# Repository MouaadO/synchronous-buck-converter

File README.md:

# 58 W Synchronous Buck Converter

**37.8–58.8 V input · 14.5 V / 4 A output target · 100 kHz · Discrete gate drivers**

This project develops a DC–DC buck converter for the auxiliary electrical network of an electric scooter. It steps the traction-battery voltage down to a 14.5 V service supply, with a design power of **58 W**. The work covers the switching stage, discrete transistor gate drivers, current and voltage sensing, LTspice simulation, and a complete two-layer KiCad PCB.

**Project team:** Amani Mouaad and Cheiffou Melissa  
**IFP SCHOOL · Powertrain · 2026/2027**

## Two projects, one conversion system

This power board is the second part of the [analog PWM generator project](https://github.com/MouaadO/analog-pwm-generator). The first board generates two complementary 5 V PWM commands with adjustable dead time. The buck board receives those signals through Arduino Uno Rev3-compatible headers, amplifies them with discrete drivers, and switches the power MOSFETs.

```mermaid
flowchart LR
    B["Scooter traction battery\n37.8–58.8 V"] --> F["Input filter"]
    F --> H["MOSFET half bridge"]
    H --> LC["Inductor + output capacitor"]
    LC --> O["Service network\n14.5 V · up to 4 A target"]
    P["Project 1\nAnalog PWM generator"] -->|"PWM1 / PWM2 + GND"| D["Discrete gate drivers\n12 V supply"]
    D --> H
    H --> M["Voltage and current sensing"]
    LC --> M
    M --> A["Analog measurement outputs\nArduino A0–A4"]
```

The intended scooter application is the **auxiliary/service electrical network**. The power path and PWM command board form an open-loop demonstrator; the measurement outputs provide an interface for later control development.

## Design targets from the project brief

| Parameter | Target |
|---|---:|
| Converter topology | Non-isolated synchronous buck |
| Battery input range | 37.8–58.8 V DC |
| Output voltage | 14.5 V |
| Maximum output current | 4 A |
| Maximum output power | 58 W |
| Switching frequency | 100 kHz |
| Inductor current ripple | 0.8 A peak to peak |
| Minimum inductance specified in the brief | 137 µH |
| Output voltage ripple target | Below 0.1% of output voltage |
| Measurement interface | 0–5 V analog signals |
| PCB outline | 166 × 53 mm |

These values are the **design specifications**, separate from the LTspice results below. The requirements come from the course mini-project brief, *Conception d’un convertisseur abaisseur de tension à redressement synchrone et de son étage de commande bas niveau*, especially pages 4–5 and 9–12.

At the rated operating point:

$$P_{out}=V_{out}I_{out}=14.5\times4=58\ \mathrm{W}$$

For an ideal buck converter, $D\approx V_{out}/V_{in}$, giving an approximate duty range of **24.7–38.4%** across the specified input range. At 100 kHz, one switching period is **10 µs**. [Design notes](docs/design.md) explain the operating sequence, component roles and sizing equations.

## How the circuit works

1. **Input filtering:** L1 filters the battery input. The 100 µF input capacitor C15 and R10 form the series damping branch used in `Newinputfilter.asc`.
2. **Discrete drivers:** NPN/PNP transistor stages translate the incoming PWM signals into MOSFET gate-drive signals. The high-side stage uses a bootstrap diode and capacitor to create a floating supply referenced to the switching node.
3. **Power conversion:** The high-side MOSFET applies the filtered input to the inductor. The low-side MOSFET provides the synchronous current path during the other part of the cycle. Complementary PWM and dead time come from the first project.
4. **Output smoothing:** The wound E25/13/7 N87 inductor and the output capacitor smooth the switched waveform into a DC output.
5. **Measurements:** Shunts, differential amplifiers, dividers and filters expose input voltage, output voltage, inductor current, filtered current and low-side current signals.

## PCB and mechanical design

The board uses **two copper layers**, predominantly through-hole components, project-local footprints and bundled 3D models. The power section groups the MOSFETs, input capacitor, shunt and output inductor. The driver components sit close to the switching stage, while measurement circuitry occupies the lower-power region.

Main load-current tracks are 2.5 mm wide, with shorter 1.2 mm connections at selected pads. Measurement tracks are 0.3 mm; gate-resistor breakouts use 0.5 mm tracks. Ground fills connect the common return network on both copper layers. A bottom-layer keepout under the switching-node area controls nearby copper placement.

### Top view

### Connection to the PWM board

The underside headers J4–J7 mate with the PWM board. The render illustrates the two-board arrangement; spacer height is an assembly choice.

| Signal | Buck connection | Uno contact |
|---|---|---|
| High-side PWM command | J4 pin 9 | D9 |
| Low-side PWM command | J4 pin 8 | D10 |
| Common ground | J4 pin 4; J6 pins 6–7 | GND |
| Input voltage measurement | J7 pin 1 | A0 |
| Output voltage measurement | J7 pin 2 | A1 |
| Inductor current measurement | J7 pin 3 | A2 |
| Filtered current measurement | J7 pin 4 | A3 |
| Low-side current measurement | J7 pin 5 | A4 |

The power input, 12 V driver supply and output load connect through separate screw terminals. [Connections and assembly](docs/connections.md) provides the complete connector map.

### Underside and stacking contacts

The downward-facing header pins connect the power board to the PWM generator. Project identification is printed on the back silkscreen.

### Front and back routing

| Front copper | Back copper |
|---|---|
|  |  |

### Heatsink and inductor mounting

The high-side MOSFET uses a TO-220 heatsink assembly. The horizontal E25 bobbin anchors the hand-wound inductor to the PCB. Local footprints define the connector positions, bobbin pin pattern and heatsink mounting slot. Manufacturer CAD and drawing-based models are bundled with the project.

## Complete schematic

Open the [KiCad schematic](pcb/Synchronous_Buck.kicad_sch) to inspect the wiring and component values at full resolution.

## LTspice simulation

The included [Newinputfilter.asc](simulation/Newinputfilter.asc) is the circuit used for the current input-filter revision. Its default testbench uses 58.8 V input, a 12 V driver supply, 100 kHz complementary PWM and a 3.625 Ω output load.

The following values are **simulation results**, measured over 6–8 ms in an 8 ms transient run:

| Quantity | Supplied-source model | Model with BOM passive values and capacitor ESR |
|---|---:|---:|
| Average output voltage | 14.504 V | 14.435 V |
| Output voltage ripple | 11.374 mV peak to peak | 69.547 mV peak to peak |
| Inductor current ripple | 0.839 A peak to peak | 0.835 A peak to peak |

Both runs use the supplied source’s active-device models. Simulation logs are included under [docs/results](docs/results). [Simulation instructions](simulation/README.md) identify the main signals to plot.

## Open and explore

1. Clone or download the complete repository.
2. Open [pcb/Synchronous_Buck.kicad_pro](pcb/Synchronous_Buck.kicad_pro) in **KiCad 8 or newer**.
3. Open the schematic or PCB Editor; press **Alt+3** in PCB Editor for the 3D viewer.
4. Keep the `Buck_Footprints.pretty`, `3dmodels`, symbol library and library tables beside the KiCad files.
5. Open `simulation/Newinputfilter.asc` in LTspice for the transient testbench.

The delivered design has **zero ERC violations, zero DRC violations and zero unrouted connections**. The source-to-schematic-to-PCB check covers **159 source-terminal connections**. Fabrication files are available in [pcb/Manufacturing](pcb/Manufacturing) and in the [Gerber/drill ZIP](pcb/Synchronous_Buck_Gerbers_Drills.zip).

## Repository contents

| Folder | Contents |
|---|---|
| `pcb/` | KiCad project, schematic, routed PCB, local libraries, 3D models and fabrication outputs |
| `simulation/` | LTspice schematic and transient simulation guide |
| `bom/` | Original purchasing workbook and current PCB assembly list |
| `docs/images/` | PCB, schematic, heatsink and stacked-board renders |
| `docs/results/` | ERC/DRC reports and LTspice measurement logs |
| `docs/design.md` | Operating principle, equations and PCB design choices |
| `docs/connections.md` | Connector map, test points and mechanical assembly |

**Related project:** [Analog PWM Generator with Adjustable Dead Time](https://github.com/MouaadO/analog-pwm-generator)

### Functional schematic sections

The complete circuit appears on one KiCad schematic sheet, arranged into eight labelled sections: power conversion, high-side driver, low-side driver, voltage measurement, inductor-current measurement and filtering, low-side current, interfaces and test points. [Schematic guide](docs/schematic-stages.md).

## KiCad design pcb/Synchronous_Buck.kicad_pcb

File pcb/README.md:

# KiCad hardware files

Open `Synchronous_Buck.kicad_pro` in KiCad 8 or newer. The complete schematic is on one A3 sheet. Open `Synchronous_Buck.kicad_pcb` in PCB Editor and press Alt+3 for the 3D viewer.

Keep `Buck.kicad_sym`, `Buck_Footprints.pretty`, `3dmodels`, `fp-lib-table` and `sym-lib-table` beside the project. The board uses two copper layers, a 166 × 53 mm outline, 1.6 mm FR4 and 35 µm / 1 oz copper as the fabrication specification.

`Manufacturing/` contains the copper, mask, silkscreen, outline and plated/non-plated drill outputs. `Synchronous_Buck_Gerbers_Drills.zip` groups the ten fabrication files. `Board_Assembly.csv` lists component references, parts and fit status; `Test_Points.csv` lists measurement points.

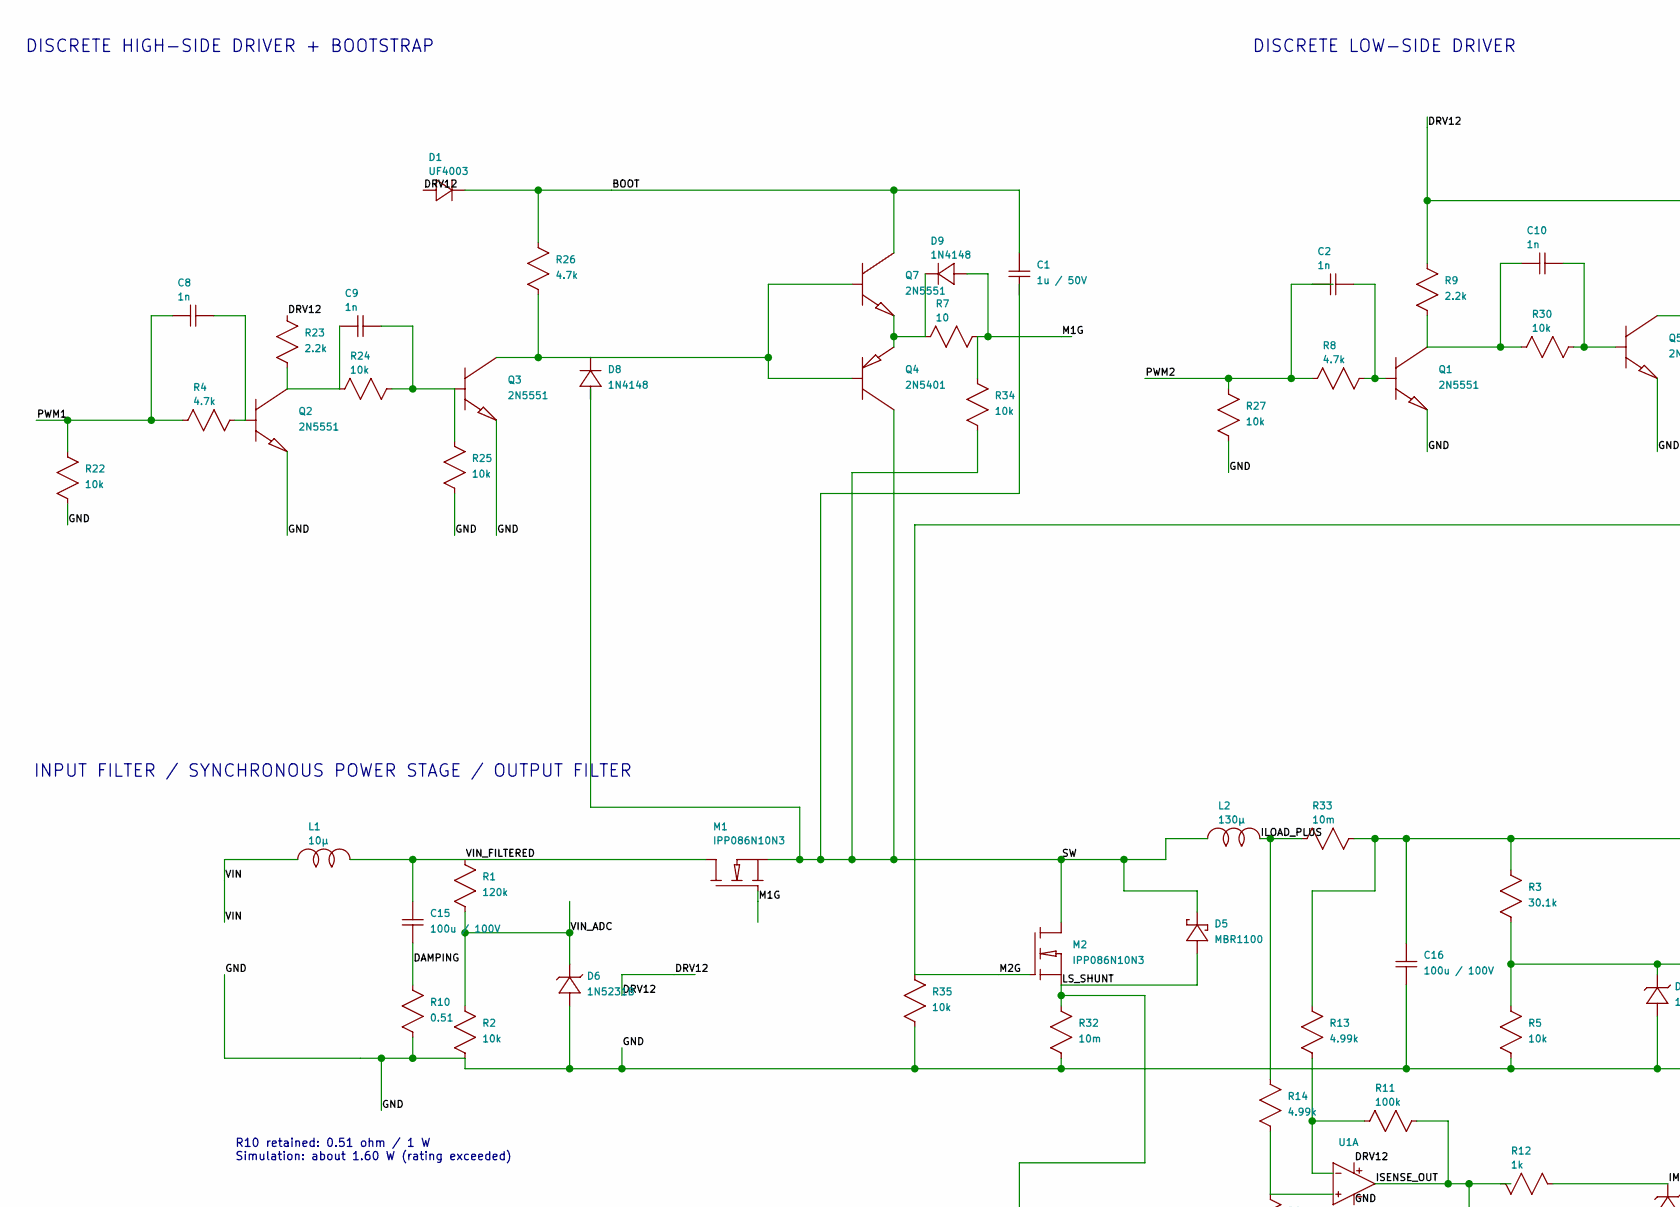
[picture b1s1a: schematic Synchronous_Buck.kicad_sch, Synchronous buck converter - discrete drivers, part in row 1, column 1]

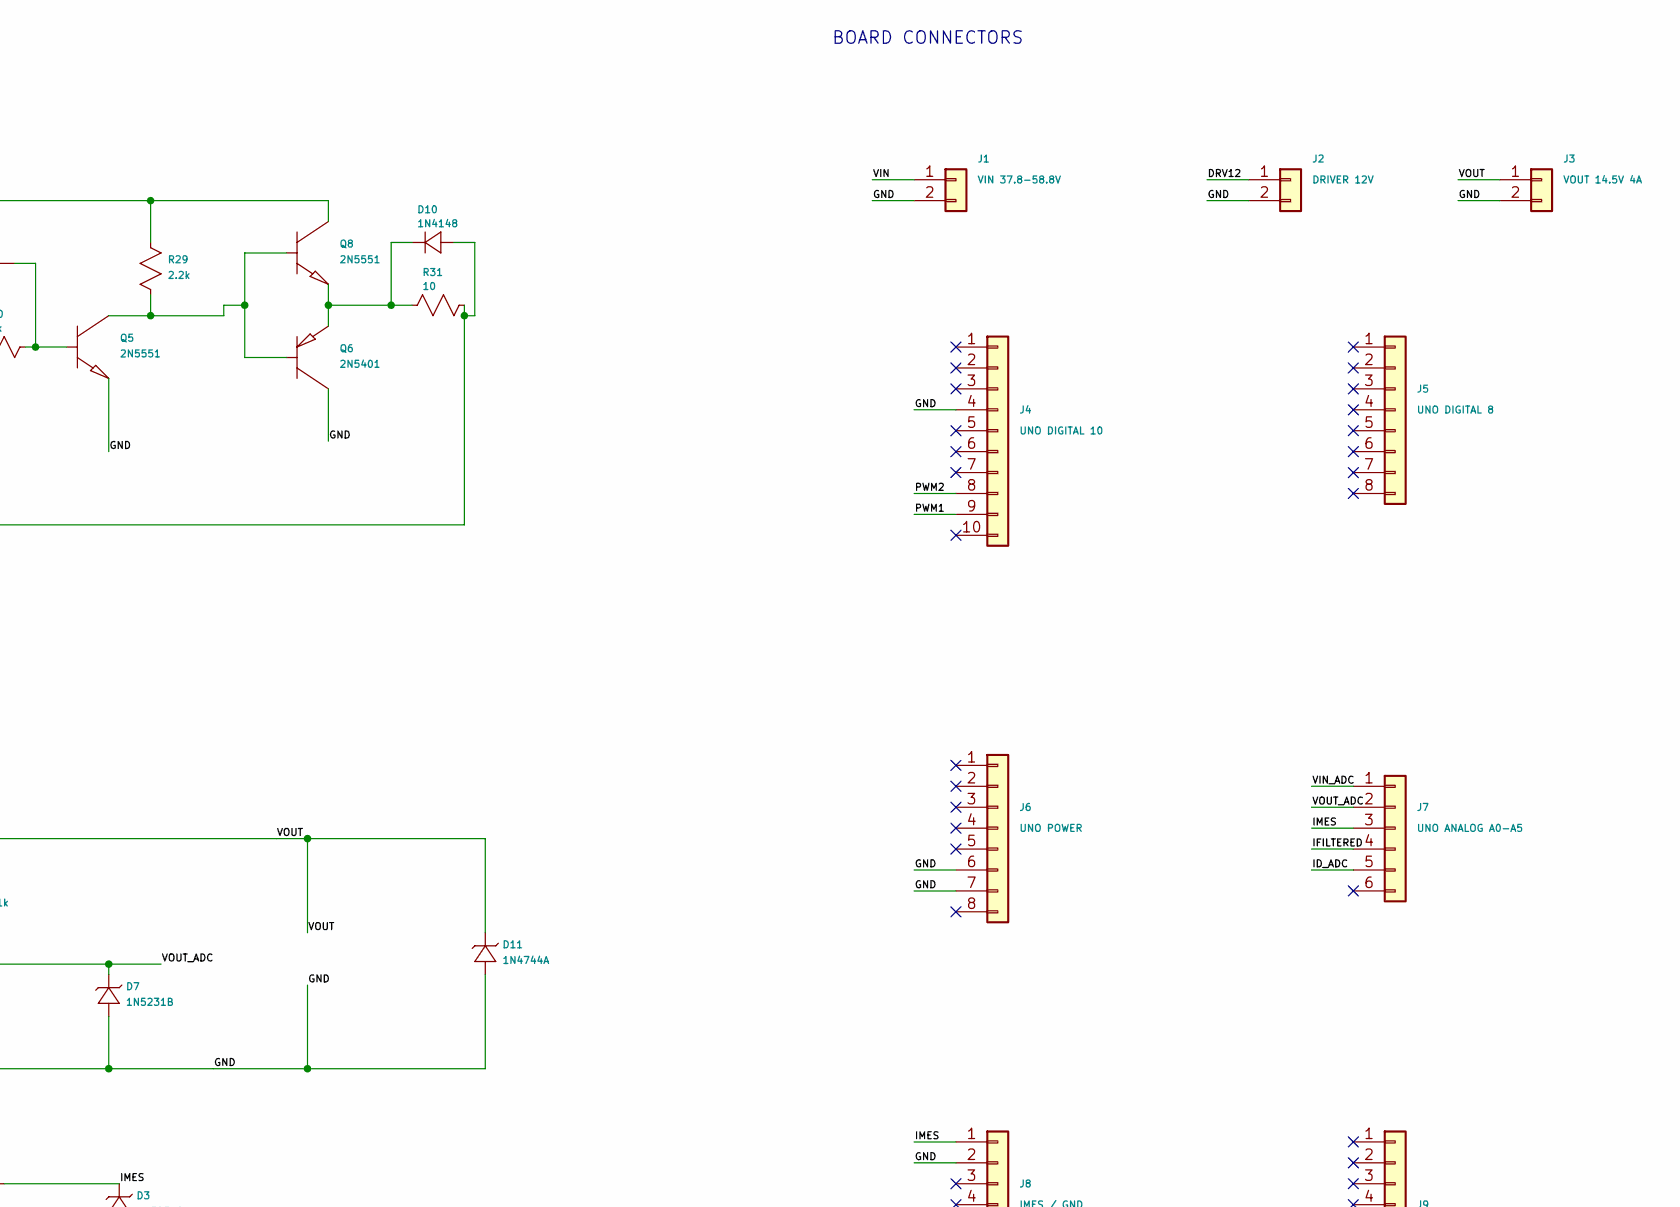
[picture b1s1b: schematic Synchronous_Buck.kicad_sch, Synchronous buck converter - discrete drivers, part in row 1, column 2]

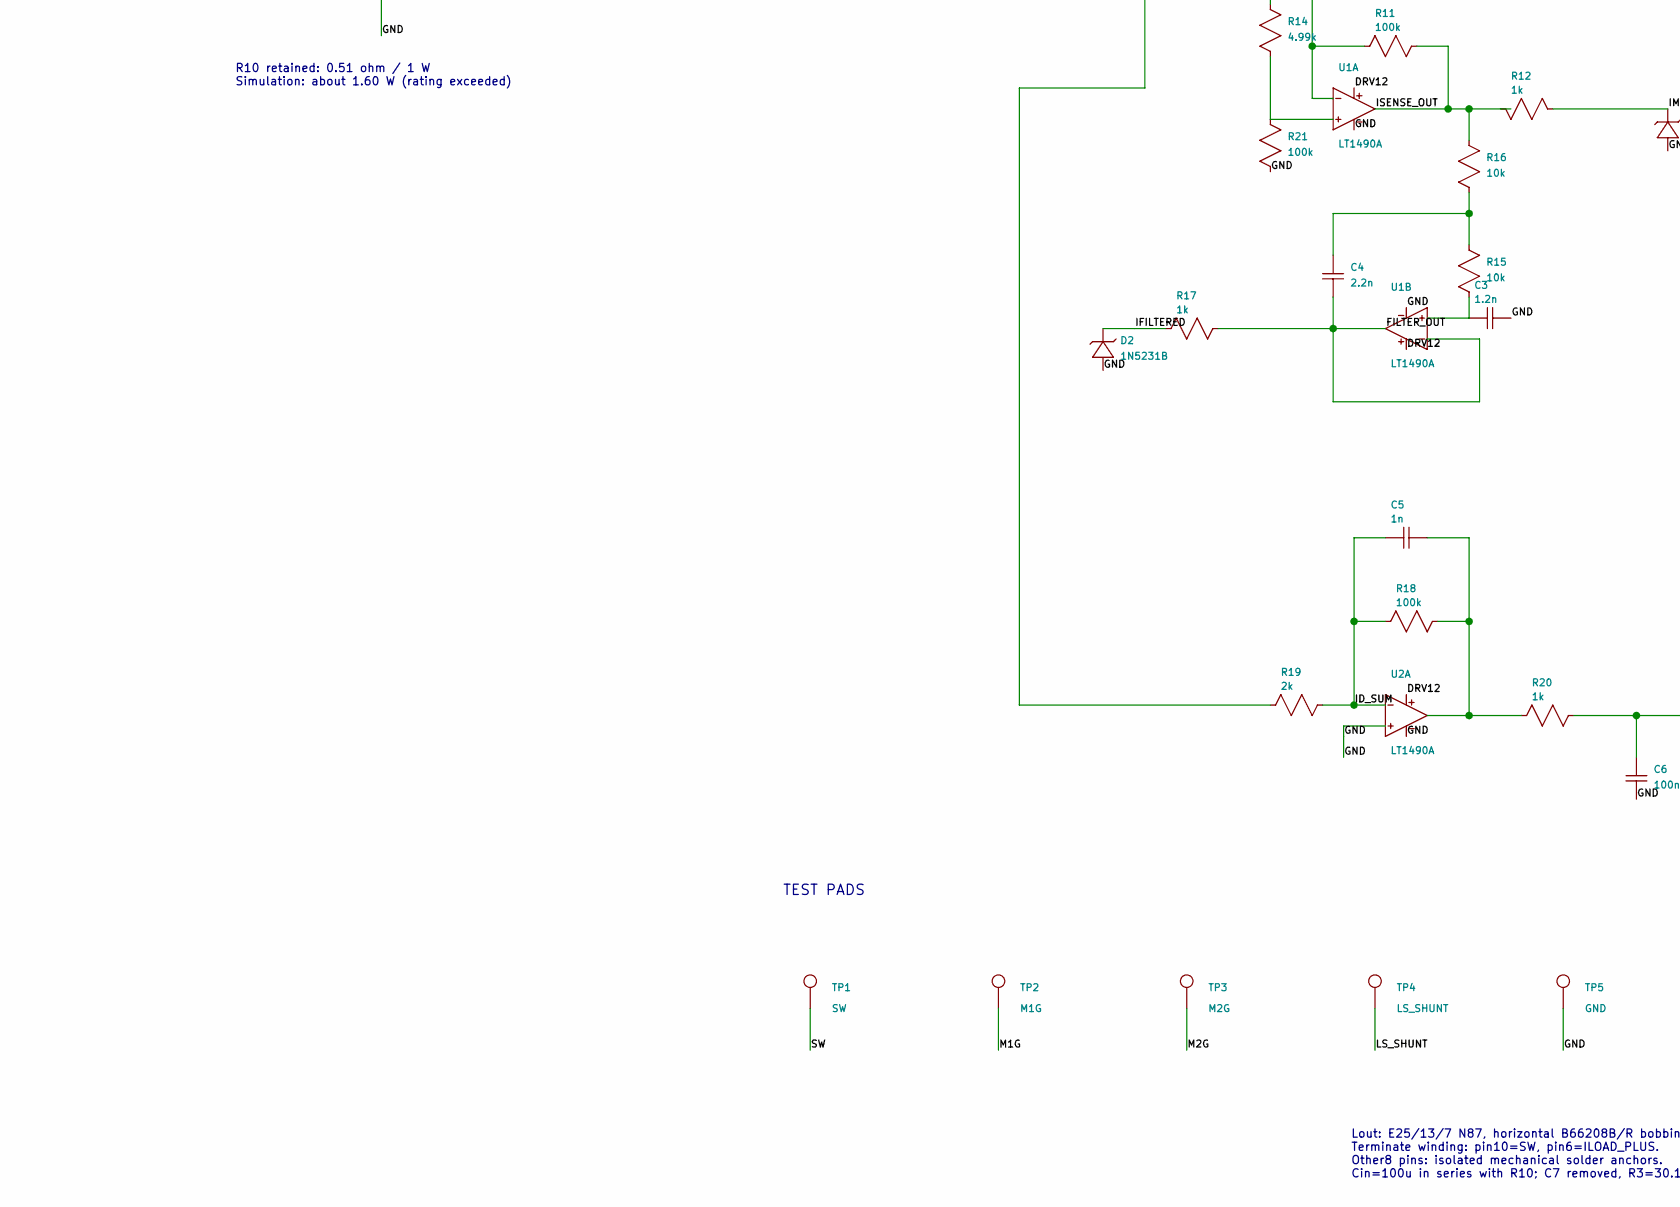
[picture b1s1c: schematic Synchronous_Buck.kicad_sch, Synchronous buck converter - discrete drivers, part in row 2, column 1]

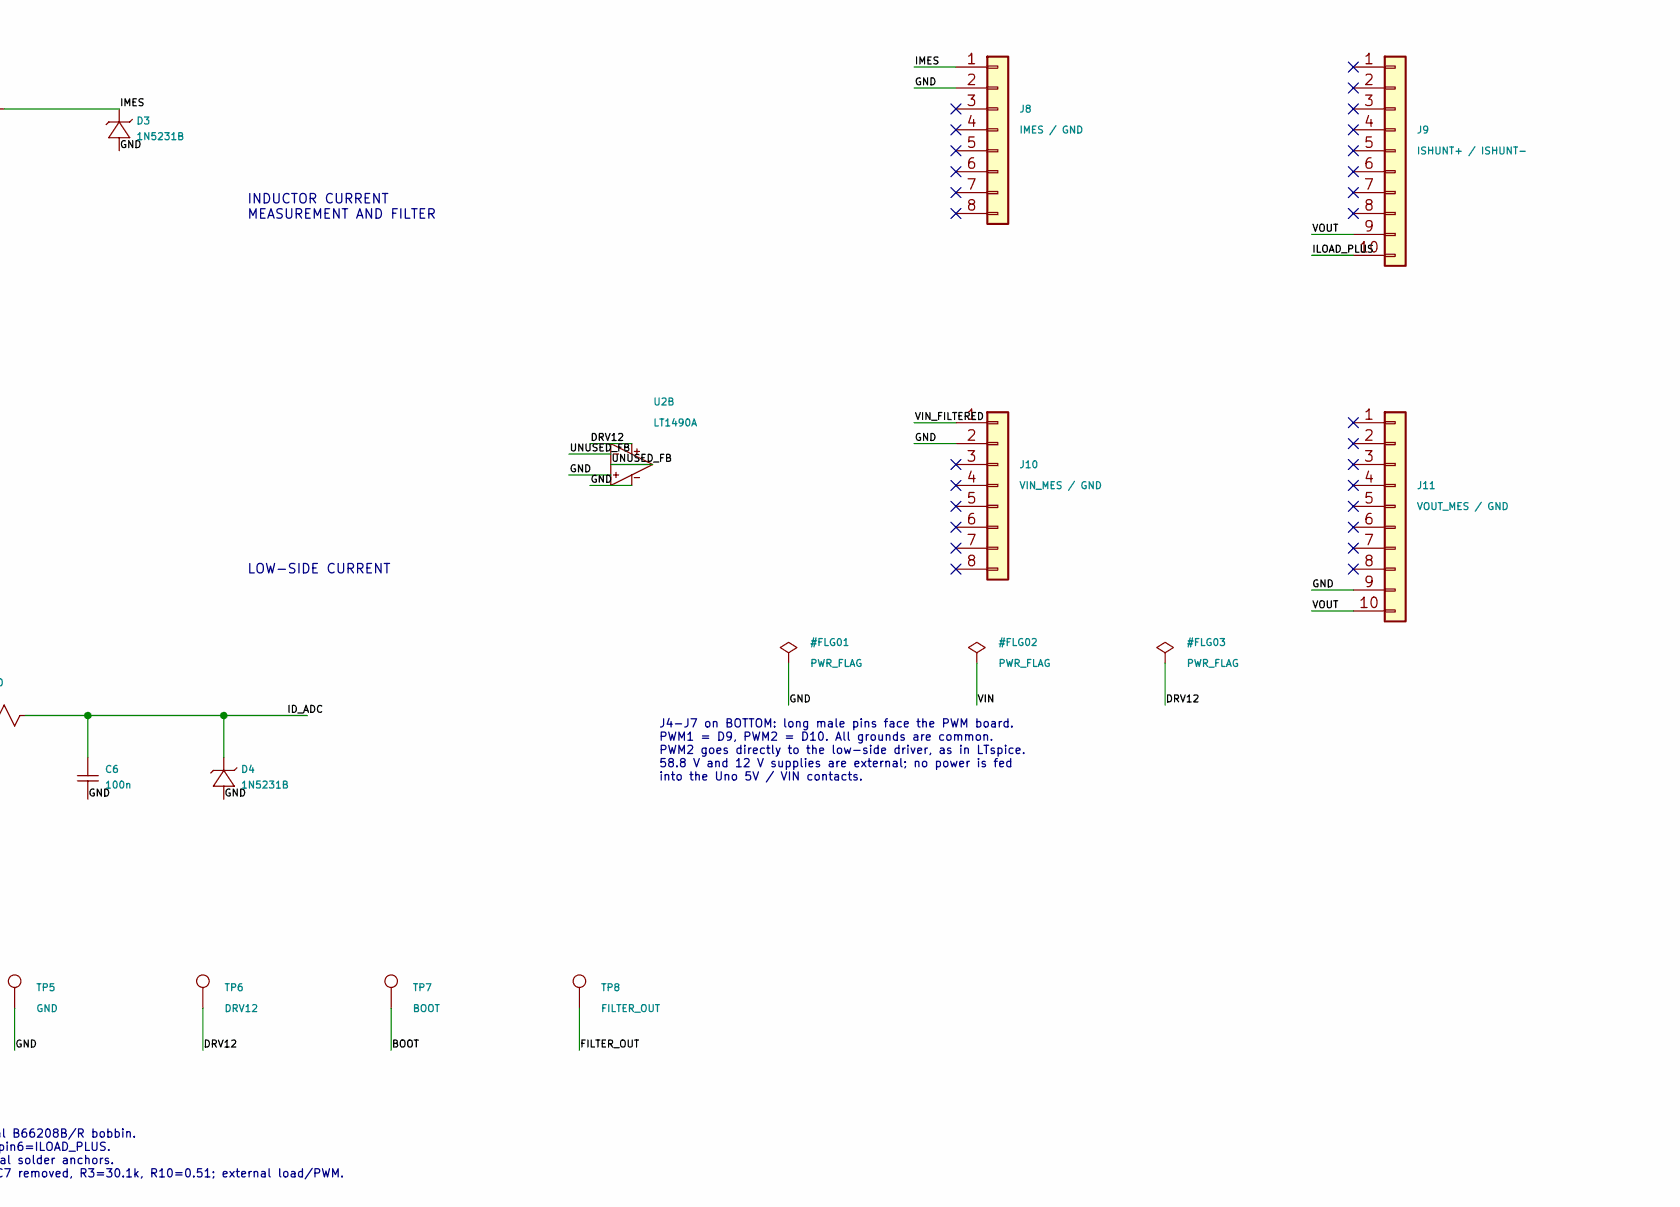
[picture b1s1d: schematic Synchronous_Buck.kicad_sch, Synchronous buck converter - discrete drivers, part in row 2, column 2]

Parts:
C1: 1u / 50V; KEMET_C330_P5.08; MPN C330C105K5R5TA7301
C2, C5, C8, C9, C10: 1n; Vishay_K15_P2.5; MPN K102K15X7RF5TL2
C3: 1.2n; KEMET_C317_P5.08; MPN C317C122J2G5TA
C4: 2.2n; KEMET_C315_P2.54; MPN C315C222F3G5TA
C6: 100n; Vishay_K15_P2.5; MPN K104K15X7RF5TL2
C15, C16: 100u / 100V; CP_Radial_D10.0mm_P5.00mm; MPN EEU-FR2A101B
D1: UF4003; D_DO-41_SOD81_P12.70mm_Horizontal; MPN UF4003-E3/54
D2, D3, D4, D6, D7: 1N5231B; D_DO-35_SOD27_P10.16mm_Horizontal; MPN 1N5231B-TR
D5: MBR1100; D_DO-41_SOD81_P12.70mm_Horizontal; MPN MBR1100RLG
D8, D9, D10: 1N4148; D_DO-35_SOD27_P10.16mm_Horizontal; MPN 1N4148-TAP
D11: 1N4744A; D_DO-41_SOD81_P12.70mm_Horizontal; MPN 1N4744A-TAP
J1: VIN 37.8-58.8V; TerminalBlock_CUI_TB007-508-02_1x02_P5.08mm_Horizontal; MPN TB007-508-02BE
J2: DRIVER 12V; TerminalBlock_CUI_TB007-508-02_1x02_P5.08mm_Horizontal; MPN TB007-508-02BE
J3: VOUT 14.5V 4A; TerminalBlock_CUI_TB007-508-02_1x02_P5.08mm_Horizontal; MPN TB007-508-02BE
J4: UNO DIGITAL 10; WE_1x10_P2.54; MPN 61304011121 cut to 10
J5: UNO DIGITAL 8; WE_1x08_P2.54; MPN 61304011121 cut to 8
J6: UNO POWER; WE_1x08_P2.54; MPN 61304011121 cut to 8
J7: UNO ANALOG A0-A5; WE_1x06_P2.54; MPN 61304011121 cut to 6
J8: IMES / GND; WE_1x08_P2.54; MPN 61304011121 cut to 8
J9: ISHUNT+ / ISHUNT-; WE_1x10_P2.54; MPN 61304011121 cut to 10
J10: VIN_MES / GND; WE_1x08_P2.54; MPN 61304011121 cut to 8
J11: VOUT_MES / GND; WE_1x10_P2.54; MPN 61304011121 cut to 10
L1: 10µ; Bourns_RLB0914_P5; MPN RLB0914-100KL
L2: 130µ; TDK_E25_B66208BR_Horizontal_10Pin_Winding10_6; MPN Hand-wound E25/13/7 N87
M1: IPP086N10N3; IPP086_with_577202; MPN IPP086N10N3GXKSA1
M2: IPP086N10N3; TO-220-3_Vertical; MPN IPP086N10N3GXKSA1
Q1, Q2, Q3, Q5, Q7, Q8: 2N5551; TO-92_Inline_Wide; MPN 2N5551TA
Q4, Q6: 2N5401; TO-92_Inline_Wide; MPN 2N5401YBU
R1: 120k; R_Axial_DIN0207_L6.3mm_D2.5mm_P10.16mm_Horizontal; MPN MFR-25FBF52-120K
R2, R5, R15, R16, R22, R24, R25, R27, R30, R34, R35: 10k; R_Axial_DIN0207_L6.3mm_D2.5mm_P10.16mm_Horizontal; MPN MFR-25FBF52-10K
R3: 30.1k; R_Axial_DIN0207_L6.3mm_D2.5mm_P10.16mm_Horizontal; MPN MFR-25FBF52-30K1
R4, R8, R26: 4.7k; R_Axial_DIN0207_L6.3mm_D2.5mm_P10.16mm_Horizontal; MPN MFR-25FBF52-4K7
R7, R31: 10; R_Axial_DIN0207_L6.3mm_D2.5mm_P10.16mm_Horizontal; MPN MFR-25FBF52-10R
R9, R23, R29: 2.2k; R_Axial_DIN0204_L3.6mm_D1.6mm_P5.08mm_Horizontal; MPN MFR25SFTF52-2K2
R10: 0.51; R_Axial_DIN0207_L6.3mm_D2.5mm_P10.16mm_Horizontal; MPN FMP100JR-52-0R51
R11, R21: 100k; R_Axial_DIN0207_L6.3mm_D2.5mm_P10.16mm_Horizontal; MPN RNF14BTC100K
R12, R17, R20: 1k; R_Axial_DIN0207_L6.3mm_D2.5mm_P10.16mm_Horizontal; MPN MFR-25FBF52-1K
R13, R14: 4.99k; R_Axial_DIN0207_L6.3mm_D2.5mm_P10.16mm_Horizontal; MPN MFR-25FBF52-4K99
R18: 100k; R_Axial_DIN0207_L6.3mm_D2.5mm_P10.16mm_Horizontal; MPN MFR-25FBF52-100K
R19: 2k; R_Axial_DIN0207_L6.3mm_D2.5mm_P10.16mm_Horizontal; MPN MFR-25FBF52-2K
R32, R33: 10m; MT2B_20.32mm; MPN MT2B-0R01F1
TP1: SW; TestPoint_Pad_D2.0mm; MPN PCB copper pad
TP2: M1G; TestPoint_Pad_D2.0mm; MPN PCB copper pad
TP3: M2G; TestPoint_Pad_D2.0mm; MPN PCB copper pad
TP4: LS_SHUNT; TestPoint_Pad_D2.0mm; MPN PCB copper pad
TP5: GND; TestPoint_Pad_D2.0mm; MPN PCB copper pad
TP6: DRV12; TestPoint_Pad_D2.0mm; MPN PCB copper pad
TP7: BOOT; TestPoint_Pad_D2.0mm; MPN PCB copper pad
TP8: FILTER_OUT; TestPoint_Pad_D2.0mm; MPN PCB copper pad
U1, U2: LT1490A; DIP-8_W7.62mm; MPN LT1490ACN8#PBF

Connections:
/BOOT: C1.1 (A), D1.1 (-), Q7.3 (C), R26.1 (A), TP7.1
/DAMPING: C15.2 (B), R10.1 (A)
/DRV12: D1.2 (+), J2.1, Q8.3 (C), R9.1 (A), R23.1 (A), R29.1 (A), TP6.1, U1.8 (V+), U2.8 (V+)
/FILTER_OUT: C4.2 (B), R17.1 (A), TP8.1, U1.6 (In-), U1.7 (OUT)
/GND: C3.1 (A), C6.2 (B), C16.2 (B), D2.2 (+), D3.2 (+), D4.2 (+), D6.2 (+), D7.2 (+), D11.2 (+), J1.2, J2.2, J3.2, J4.4, J6.6, J6.7, J8.2, J10.2, J11.9, Q1.1 (E), Q2.1 (E), Q3.1 (E), Q5.1 (E), Q6.3 (C), R2.2 (B), R5.2 (B), R10.2 (B), R21.2 (B), R22.2 (B), R25.2 (B), R27.2 (B), R32.2 (B), R35.2 (B), TP5.1, U1.4 (V-), U2.3 (In+), U2.4 (V-), U2.5 (In+)
/ID_ADC: C6.1 (A), D4.1 (-), J7.5, R20.1 (A)
/ID_SUM: C5.2 (B), R18.2 (B), R19.1 (A), U2.2 (In-)
/IFILTERED: D2.1 (-), J7.4, R17.2 (B)
/ILOAD_PLUS: J9.10, L2.6 (B), R14.1 (A), R33.2 (B)
/IMES: D3.1 (-), J7.3, J8.1, R12.2 (B)
/ISENSE_OUT: R11.1 (A), R12.1 (A), R16.1 (A), U1.1 (OUT)
/LS_SHUNT: D5.2 (+), M2.3 (S), R19.2 (B), R32.1 (A), TP4.1
/M1G: D9.2 (+), M1.1 (G), R7.1 (A), R34.1 (A), TP2.1
/M2G: D10.2 (+), M2.1 (G), R31.1 (A), R35.1 (A), TP3.1
/PWM1: C8.2 (B), J4.9, R4.2 (B), R22.1 (A)
/PWM2: C2.2 (B), J4.8, R8.2 (B), R27.1 (A)
/SW: C1.2 (B), D5.1 (-), D8.2 (+), L2.10 (A), M1.3 (S), M2.2 (D), Q4.3 (C), R34.2 (B), TP1.1
/UNUSED_FB: U2.6 (In-), U2.7 (OUT)
/VIN: J1.1, L1.1 (A)
/VIN_ADC: D6.1 (-), J7.1, R1.2 (B), R2.1 (A)
/VIN_FILTERED: C15.1 (A), J10.1, L1.2 (B), M1.2 (D), R1.1 (A)
/VOUT: C16.1 (A), D11.1 (-), J3.1, J9.9, J11.10, R3.1 (A), R13.1 (A), R33.1 (A)
/VOUT_ADC: D7.1 (-), J7.2, R3.2 (B), R5.1 (A)
unnamed: C2.1 (A), Q1.2 (B), R8.1 (A)
unnamed: C3.2 (B), R15.2 (B), U1.5 (In+)
unnamed: C4.1 (A), R15.1 (A), R16.2 (B)
unnamed: C5.1 (A), R18.1 (A), R20.2 (B), U2.1 (OUT)
unnamed: C8.1 (A), Q2.2 (B), R4.1 (A)
unnamed: C9.1 (A), Q3.2 (B), R24.1 (A), R25.1 (A)
unnamed: C9.2 (B), Q2.3 (C), R23.2 (B), R24.2 (B)
unnamed: C10.1 (A), Q5.2 (B), R30.1 (A)
unnamed: C10.2 (B), Q1.3 (C), R9.2 (B), R30.2 (B)
unnamed: D8.1 (-), Q3.3 (C), Q4.2 (B), Q7.2 (B), R26.2 (B)
unnamed: D9.1 (-), Q4.1 (E), Q7.1 (E), R7.2 (B)
unnamed: D10.1 (-), Q6.1 (E), Q8.1 (E), R31.2 (B)
unnamed: Q5.3 (C), Q6.2 (B), Q8.2 (B), R29.2 (B)
unnamed: R11.2 (B), R13.2 (B), U1.2 (In-)
unnamed: R14.2 (B), R21.1 (A), U1.3 (In+)

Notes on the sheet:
DISCRETE HIGH-SIDE DRIVER + BOOTSTRAP
DISCRETE LOW-SIDE DRIVER
INPUT FILTER / SYNCHRONOUS POWER STAGE / OUTPUT FILTER
INDUCTOR CURRENT MEASUREMENT AND FILTER
LOW-SIDE CURRENT
BOARD CONNECTORS
J4-J7 on BOTTOM: long male pins face the PWM board. PWM1 = D9, PWM2 = D10. All grounds are common. PWM2 goes directly to the low-side driver, as in LTspice. 58.8 V and 12 V supplies are external; no power is fed into the Uno 5V / VIN contacts.
TEST PADS
Lout: E25/13/7 N87, horizontal B66208B/R bobbin. Terminate winding: pin10=SW, pin6=ILOAD_PLUS. Other8 pins: isolated mechanical solder anchors. Cin=100u in series with R10; C7 removed, R3=30.1k, R10=0.51; external load/PWM.
R10 retained: 0.51 ohm / 1 W Simulation: about 1.60 W (rating exceeded)

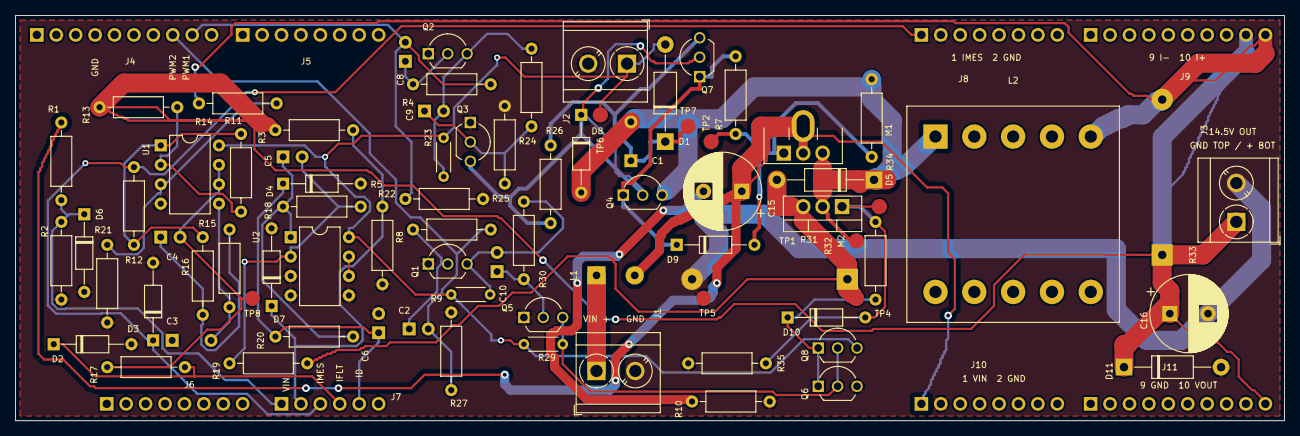
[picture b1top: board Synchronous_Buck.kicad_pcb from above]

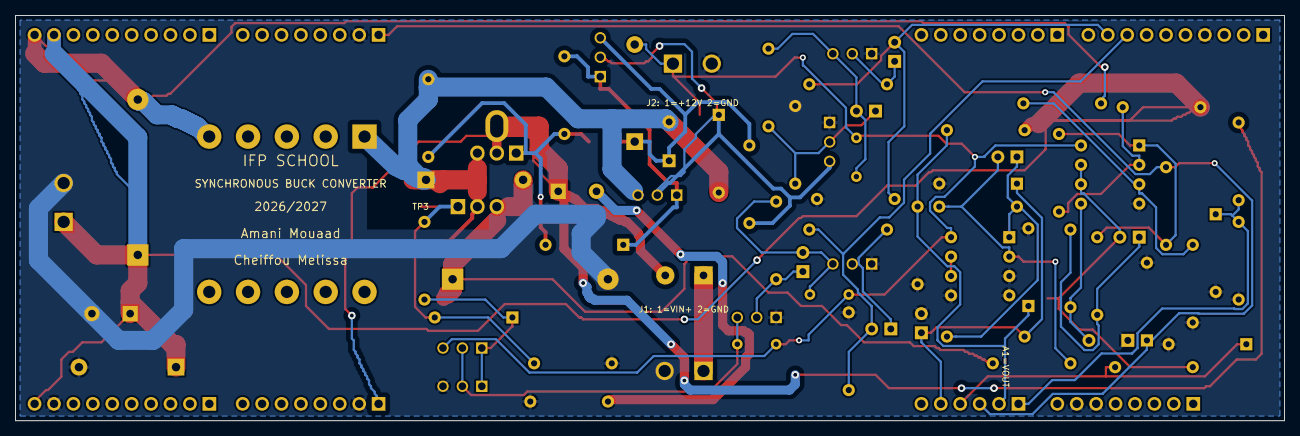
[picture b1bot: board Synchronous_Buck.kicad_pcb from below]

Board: 2 copper layers, 166.0 x 53.0 mm, 88 parts (4 on the bottom side), 38 nets.

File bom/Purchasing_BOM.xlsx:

| Synchronous buck converter · Bill of materials
 | 37.8–58.8 V → 14.5 V / 4 A · 100 kHz · all through-hole · IFP Powertrain mini-p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
 |  | Total excl. VAT | 42.971000000000011
 |  | VAT rate | 0.2
 |  | Total incl. VAT | 51.565200000000011
 | Schematic ref (LTspice) | Simulated model | Description | Manufacturer | Manufacturer PN | Order qty | Retailer | Retailer PN | Unit € excl. VAT | Line € excl. VAT | Order link
 | Power stage
 | Lin | 10µ | 10 µH inductor · Irms 2.7 A · Isat 6.7 A · 48 mΩ | Bourns | RLB0914-100KL | 1 | Farnell | 2321765 | 0.34 | 0.34 | Open Farnell ↗
 | Cin, Cout | 100µ | 100 µF capacitor · 100 V · low-ESR electrolytic (FR series) · 1.5 A ripple at 1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 | Panasonic | EEU-FR2A101B | 2 | Mouser | 667-EEU-FR2A101B | 1.22 | 2.44 | Open Mouser ↗
 | C7 | 10µ | 10 µF capacitor · 100 V · 20% electrolytic · damping branch | Panasonic | ECA2AM100 | 1 | Farnell | 9693912 | 0.21 | 0.21 | Open Farnell ↗
 | R10 | 0.5 | 0.5 Ω resistor · 5% · 1 W | Yageo | FMP100JR-52-0R51 | 1 | Mouser | 603-FMP100JR-52-0R51 | 0.33500000000000002 | 0.33500000000000002 | Open Mouser ↗
 | M1, M2 | IPP086N10N3 | N-MOSFET · 100 V · 8.6 mΩ · 80 A · Qg 55 nC · TO-220 | Infineon | IPP086N10N3GXKSA1 | 2 | Farnell | 2709893 | 2.65 | 5.3 | Open Farnell ↗
 | D5 | MBRS1100 | Schottky rectifier · 100 V · 1 A · DO-41 | onsemi | MBR1100RLG | 1 | Mouser | 863-MBR1100RLG | 0.69699999999999995 | 0.69699999999999995 | Open Mouser ↗
 | Rshunt, Rshunt2 | 10m | 10 mΩ current sense resistor · 1% | Riedon (Bourns) | MT2B-0R01F1 | 2 | DigiKey | 696-1734-ND | 2.41 | 4.82 | Open DigiKey ↗
 | D11 | BZX84C15L | Zener Diodes 15 Volt 1.3 Watt | Vishay Semiconductors | 1N4744A-TAP | 1 | Mouser | 78-1N4744A-TAP | 0.33500000000000002 | 0.33500000000000002 | Open Mouser ↗
 | Gate drivers (M1 high side, M2 low side)
 | D1 | MMSD4148 | Ultrafast diode · 200 V · 1 A · 50 ns · DO-41 (bootstrap) | Vishay | UF4003-E3/54 | 5 | Farnell | 9551646 | 0.70599999999999996 | 3.53 | Open Farnell ↗
 | C1 | 1µ | 1 µF capacitor · 50 V · X7R · 10% (bootstrap) | KEMET | C330C105K5R5TA7301 | 1 | Mouser | 80-C330C105K5R7301 | 0.57599999999999996 | 0.57599999999999996 | Open Mouser ↗
 | Q1, Q2, Q3, Q5, Q7, Q8 | BC846B / 2SC4061K | NPN transistor · 160 V · 600 mA · 0.625 W · hFE ≥ 80 (all NPN: inverters, level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 | onsemi | 2N5551TA | 6 | DigiKey | 2N5551TAFSCT-ND | 0.27 | 1.62 | Open Digikey ↗
 | Q4, Q6 | BC556B | PNP transistor · 150 V · 600 mA · 0.625 W · complement of 2N5551 (totem bottoms) | onsemi | 2N5401YBU | 2 | DigiKey | 2N5401YBUOS-ND | 0.26 | 0.52 | Open DigiKey ↗
 | D8, D9, D10 | D (default) | Small-signal diode · 100 V · 150 mA · 4 ns · DO-35 | Vishay | 1N4148-TAP | 3 | Mouser | 78-1N4148-TAP | 0.224 | 0.67200000000000004 | Open Mouser ↗
 | R7, R31 | 10 | 10 Ω resistor · 1% · 0.25 W (gate) | Yageo | MFR-25FBF52-10R | 2 | Mouser | 603-MFR-25FBF52-10R | 8.5999999999999993E-2 | 0.17199999999999999 | Open Mouser ↗
 | R4, R8, R26 | 4.7k | 4.7 kΩ resistor · 1% · 0.25 W | Yageo | MFR-25FBF52-4K7 | 3 | Mouser | 603-MFR-25FBF52-4K7 | 9.5000000000000001E-2 | 0.28500000000000003 | Open Mouser ↗
 | R9, R23, R29 | 2.2k | 2.2 kΩ resistor · 1% · 0.25 W | Yageo | MFR25SFTF52-2K2 | 3 | DigiKey | MFR25SFTF52-2K2 | 0.1 | 0.30000000000000004 | Open DigiKey ↗
 | C2, C5, C8, C9, C10 | 1n | 1 nF capacitor · 50 V · X7R · 10% (speed-up) | Vishay | K102K15X7RF5TL2 | 5 | Mouser | 594-K102K15X7RF5TL2 | 0.224 | 1.1200000000000001 | Open Mouser ↗
 | Shared resistors
 | R2, R5, R15, R16, R22, R24, R25, R27, R30, Rgate1, Rgate2 | 10k | 10 kΩ resistor · 1% · 0.25 W | Yageo | MFR-25FBF52-10K | 11 | Mouser | 603-MFR-25FBF52-10K | 8.5999999999999993E-2 | 0.94599999999999995 | Open Mouser ↗
 | R12, R17, R20 | 1k | 1 kΩ resistor · 1% · 0.25 W | Yageo | MFR-25FBF52-1K | 3 | Mouser | 603-MFR-25FBF52-1K | 8.5999999999999993E-2 | 0.25800000000000001 | Open Mouser ↗
 | Measurements for the Arduino
 | R1 | 120k | 120 kΩ resistor · 1% · 0.25 W (Vin ÷13) | Yageo | MFR-25FBF52-120K | 1 | Mouser | 603-MFR-25FBF52-120K | 0.18099999999999999 | 0.18099999999999999 | Open Mouser ↗
 | R3 | 30k | 30.1 kΩ resistor · 1% · 0.25 W (Vout ÷4) | Yageo | MFR-25FBF52-30K1 | 1 | Mouser | 603-MFR-25FBF52-30K1 | 8.5999999999999993E-2 | 8.5999999999999993E-2 | Open Mouser ↗
 | R13, R14 | 4.99k | 4.99 kΩ resistor · 1% · 0.25 W | Yageo | MFR-25FBF52-4K99 | 2 | Mouser | 603-MFR-25FBF52-4K99 | 8.5999999999999993E-2 | 0.17199999999999999 | Open Mouser ↗
 | R11, R21 | 100k | 100 kΩ resistor · 0.1% · 0.25 W | SEI Stackpole | RNF14BTC100K | 2 | Mouser | 708-RNF14BTC100K | 0.108 | 0.216 | Open Mouser ↗
 | R18 | 100k | 100 kΩ resistor · 1% · 0.25 W | Yageo | MFR-25FBF52-100K | 1 | Mouser | 603-MFR-25FBF52-100K | 8.5999999999999993E-2 | 8.5999999999999993E-2 | Open Mouser ↗
 | R19 | 2k | 2 kΩ resistor · 1% · 0.25 W | Yageo | MFR-25FBF52-2K | 1 | Mouser | 603-MFR-25FBF52-2K | 8.5999999999999993E-2 | 8.5999999999999993E-2 | Open Mouser ↗
 | U1, U2, U4 (+1 spare) | LT1490 | Dual Over-The-Top op amp · 44 V inputs · rail-to-rail | Analog Devices | LT1490ACN8#PBF | 2 | Farnell | LT1490ACN8#PBF | 5.28 | 10.56 | Open Farnell ↗
 | D2, D3, D4, D6, D7 | UMZ5_1N | 5.1 V Zener diode · 500 mW · DO-35 (ADC clamp) | Vishay | 1N5231B-TR | 5 | Mouser | 78-1N5231B | 0.42099999999999999 | 2.105 | Open Mouser ↗
 | C3 | 1.2n | 1.2 nF ceramic capacitor · 200 V | KEMET | C317C122J2G5TA | 1 | Mouser | 80-C317C122J2G5TA | 0.63600000000000001 | 0.63600000000000001 | Open Mouser ↗
 | C4 | 2.2n | 2.2 nF capacitor · 25 V · C0G · 1% (filter) | KEMET | C315C222F3G5TA | 1 | Mouser | 80-C315C222F3G5TA | 1.19 | 1.19 | Open Mouser ↗
 | C6 | 100n | 100 nF capacitor · 50 V · X7R · 10% | Vishay | K104K15X7RF5TL2 | 1 | Mouser | 594-K104K15X7RF5TL2 | 0.26700000000000002 | 0.26700000000000002 | Open Mouser ↗
 | Connectors
 | Headers 10-pin ×2 | — (not simulated) | Male header · 1×10 · 2.54 mm · tin | Wurth Elektronik | 61304011121 | 1 | Mouser | 710-61304011121 | 1.32 | 1.32 | Open Mouser ↗
 | Supply terminals ×3 | — (not simulated) | Terminal block · screw type · 2 pos · 5.08 mm | Same Sky | TB007-508-02BE | 3 | DigiKey | TB007-508-02BE | 0.53 | 1.59 | Open DigiKey ↗
 | Heat sink for M1 | — (not simulated) | Heat Sinks Channel Heat Sink for TO220, Vertical, 24.4 Degree C/W | Aavid | 577202B04000G | 1 | Mouser | 532-577202B04000G | 1.0900000000000001 | 1.0900000000000001 | Open Mouser ↗
